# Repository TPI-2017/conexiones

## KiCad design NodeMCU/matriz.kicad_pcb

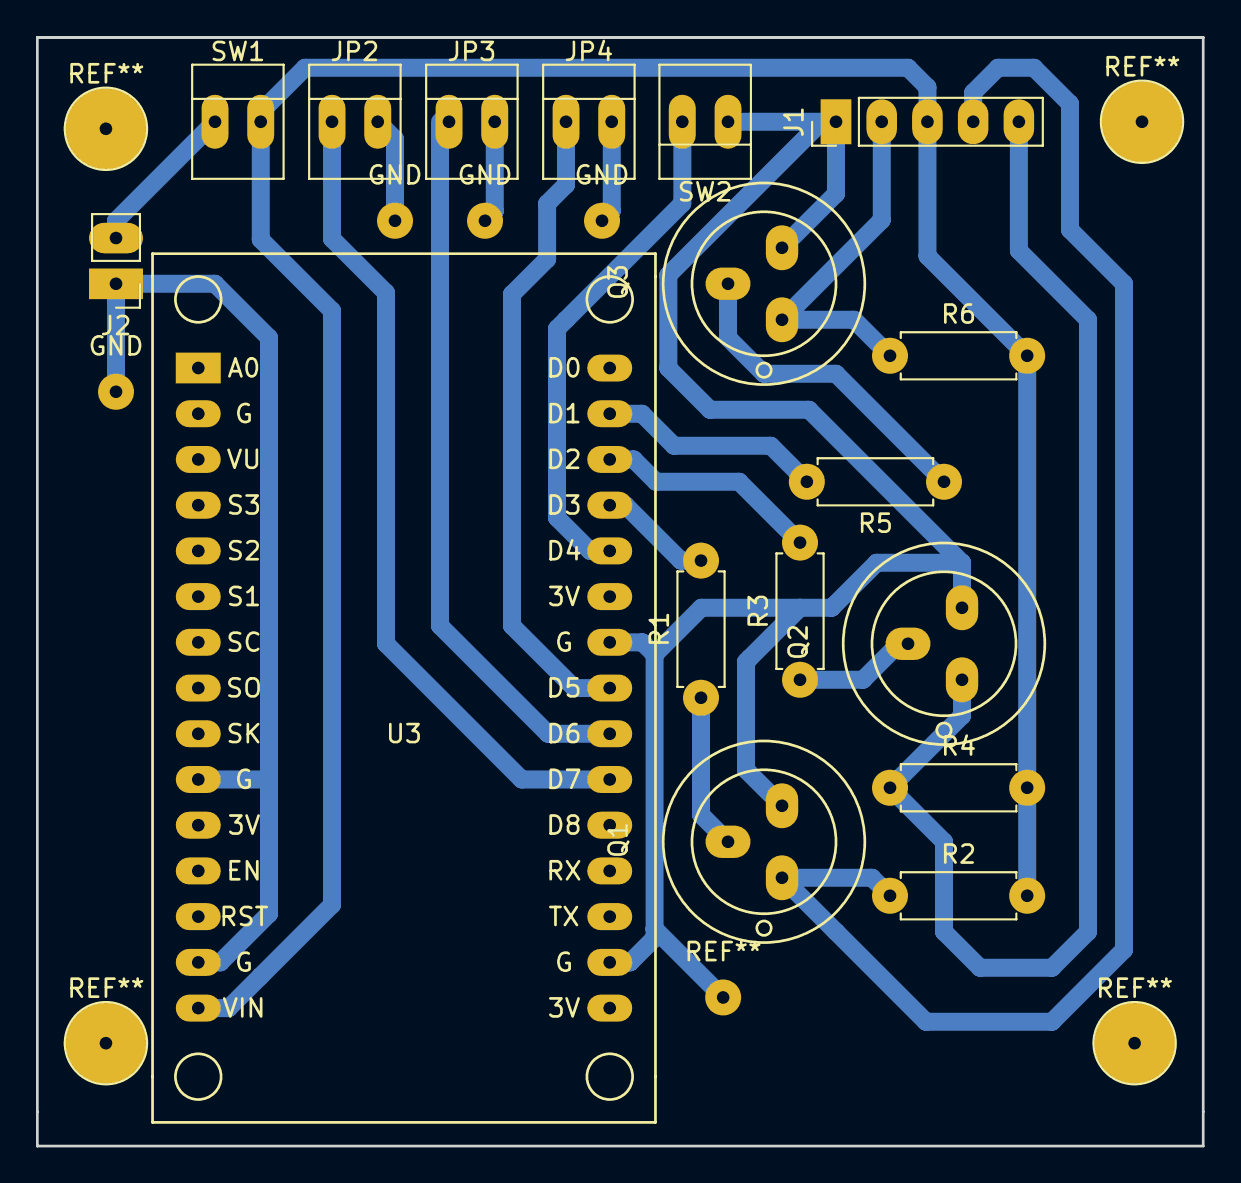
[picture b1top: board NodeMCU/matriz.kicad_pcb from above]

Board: 2 copper layers, 64.8 x 61.6 mm, 21 parts (0 on the bottom side), 16 nets.

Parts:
GND: SolderWirePad_single_0-8mmDrill
GND#2, GND#3, GND#4: SolderWirePad_single_0-8mmDrill
J1: Conn_01x05; Pin_Header_Straight_1x05_Pitch2.54mm
J2: Conn_01x02; Pin_Header_Straight_1x02_Pitch2.54mm
JP2, JP3, JP4: Jp_open_small; PINHEAD1-2
Q1, Q2, Q3: Q_NPN_CBE; OldSowjetaera_Transistor_Type-II_BigPads
R1, R2, R3, R4, R5, R6: 10KOhm; R_Axial_DIN0207_L6.3mm_D2.5mm_P7.62mm_Horizontal
SW1: SW_Push_Open; PINHEAD1-2
SW2: SW_Push; PINHEAD1-2
U3: NodeMCU1.0(ESP-12E); NodeMCU1.0(12-E)

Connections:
/CLK: J1.4, Q1.1, R2.1
/DOUT: J1.2, Q3.1, R6.1
/GND: GND.1, GND#2.1, GND#3.1, GND#4.1, J1.1, J2.1, JP2.2, JP3.2, JP4.2, Q1.3, Q2.3, Q3.3, SW2.1, U3.10, U3.14, U3.17, U3.24
/LD: J1.5, Q2.1, R4.1
/PWR: J2.2, SW1.1
/V+: J1.3, R2.2, R4.2, R6.2, SW1.2, U3.15
unnamed: JP2.1, U3.21
unnamed: JP3.1, U3.22
unnamed: JP4.1, U3.23
unnamed: Q1.2, R1.1
unnamed: Q2.2, R3.1
unnamed: Q3.2, R5.1
unnamed: R1.2, U3.27
unnamed: R3.2, U3.28
unnamed: R5.2, U3.29
unnamed: SW2.2, U3.26

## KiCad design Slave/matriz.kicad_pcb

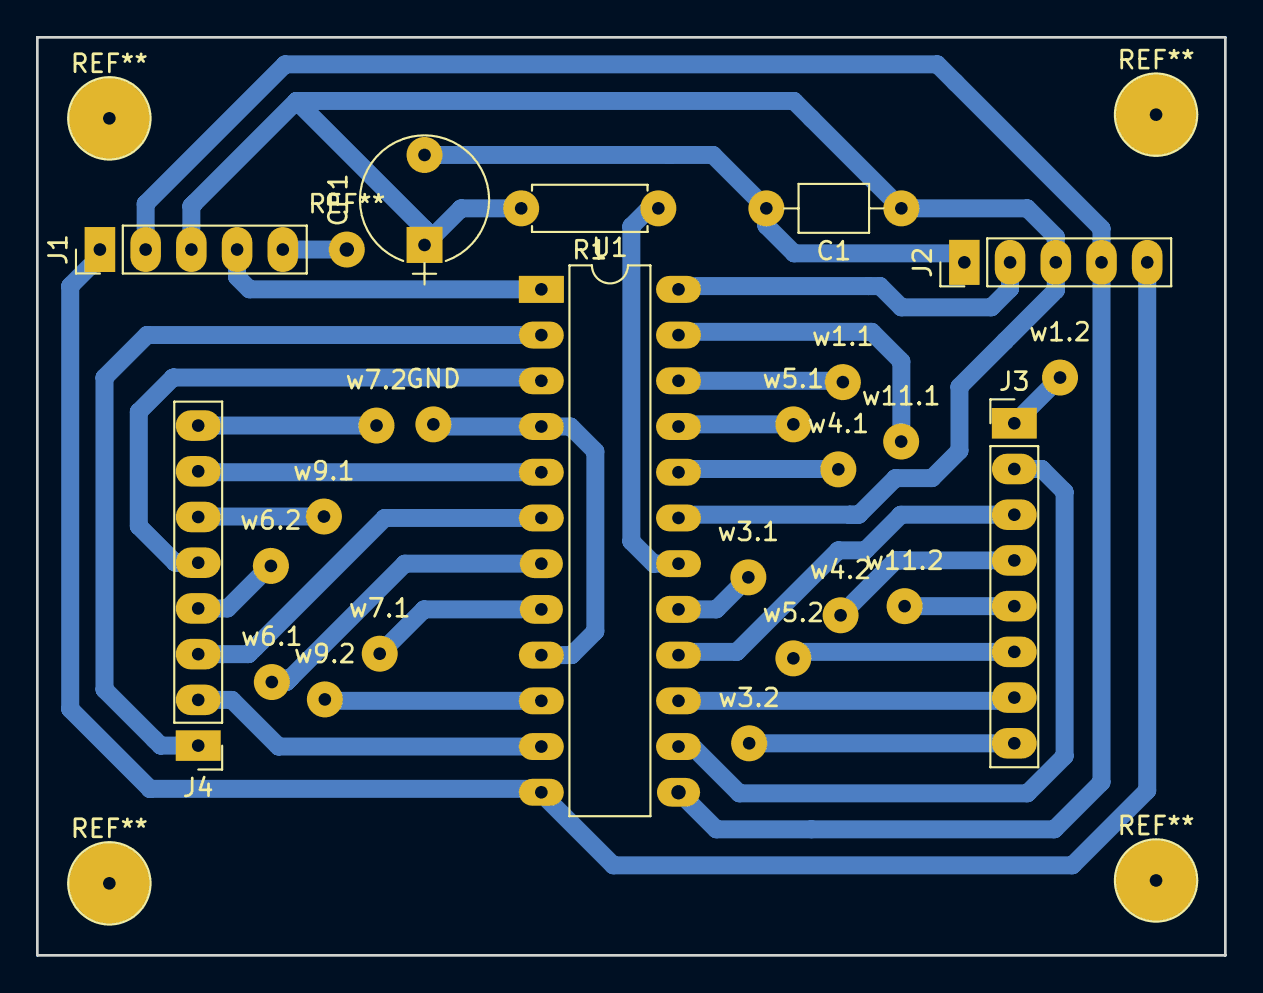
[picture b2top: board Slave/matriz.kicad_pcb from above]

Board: 2 copper layers, 66.0 x 51.0 mm, 25 parts (0 on the bottom side), 23 nets.

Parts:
C1: 0.1µF; C_Axial_L3.8mm_D2.6mm_P7.50mm_Horizontal
CP1: 10µF; CP_Radial_Tantal_D7.0mm_P5.00mm
GND: SolderWirePad_single_0-8mmDrill
J1, J2: Conn_01x05; Pin_Header_Straight_1x05_Pitch2.54mm
J3, J4: Conn_01x08; Pin_Header_Straight_1x08_Pitch2.54mm
R1: 24kOhm; R_Axial_DIN0207_L6.3mm_D2.5mm_P7.62mm_Horizontal
U1: MAX7219; DIP-24_W7.62mm_LongPads
w1.1, w1.2, w3.1, w3.2, w4.1, w4.2, w5.1, w5.2, w6.1, w6.2, w7.1, w7.2, w9.1, w9.2, w11.1, w11.2: SolderWirePad_single_0-8mmDrill

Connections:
/C0: J4.1, U1.2
/C1: J4.2, U1.e11
/C2: J4.3, U1.6
/C3: J4.4, U1.7, w6.1.1, w6.2.1
/C4: J4.5, U1.3
/C5: J4.6, U1.10, w9.1.1, w9.2.1
/C6: J4.7, U1.5
/C7: J4.8, U1.8, w7.1.1, w7.2.1
/CLK: J1.2, J2.4, U1.13
/DIN: J1.4, U1.1
/DOUT: J2.2, U1.24
/F0: J3.8, U1.17, w3.1.1, w3.2.1
/F1: J3.7, U1.15
/F2: J3.6, U1.21, w5.1.1, w5.2.1
/F3: J3.5, U1.23, w11.1.1, w11.2.1
/F4: J3.4, U1.20, w4.1.1, w4.2.1
/F5: J3.3, U1.16
/F6: J3.2, U1.14
/F7: J3.1, U1.22, w1.1.1, w1.2.1
/GND: C1.2, CP1.2, GND.1, J1.5, J2.1, U1.4, U1.9
/LD: J1.1, J2.5, U1.12
/V+: C1.1, CP1.1, J1.3, J2.3, R1.2, U1.19
unnamed: R1.1, U1.18

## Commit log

2017-10-22 Init project and more
2017-10-24 Actualizaciones importantes en el esquema y error unidad capacitor
2017-10-25 Modificaciones menores
2017-11-05 hola soy un commit hecho por nahuel # with '#' will be ignored, and an empty message aborts the commit. #
2017-11-06 Cosas
2017-11-06 Sin labels y mas
2017-11-10 Mega commit con la modularizacion planteada en clase
2017-11-10 Fix menores
2017-11-13 Actualizacion diseño FINAL con santi
2017-11-13 Esquematico testeado
2017-11-19 Footprint slave
2017-11-27 finished the slave design and printed the mirrored final layout
2017-11-27 something changed in slave files before closing so this commit got that covered
2017-11-29 master changes
2017-11-29 avances master
2017-11-30 Cosas del dia 30 en barcara
2017-11-30 Pistas todas de 1mm, limite y unidades mecanicas
2017-12-04 Saco un jumprs y reacomodo
2017-12-04 Pongo las pistas en para que sea lo de atras (en verde) y minimiso espacio
2017-12-09 Avances entre todos
2017-12-09 Generacion de pdf final con limites y otras cosas
2017-12-12 Ultimos cambios
2017-12-13 Pads adecuados
2017-12-13 Este es un commit para rama
2017-12-14 esta comiendo una empanada
